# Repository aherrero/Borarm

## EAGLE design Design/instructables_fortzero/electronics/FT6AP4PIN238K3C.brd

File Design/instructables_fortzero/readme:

http://www.instructables.com/id/4-Axis-Robot-Arm-DIY/

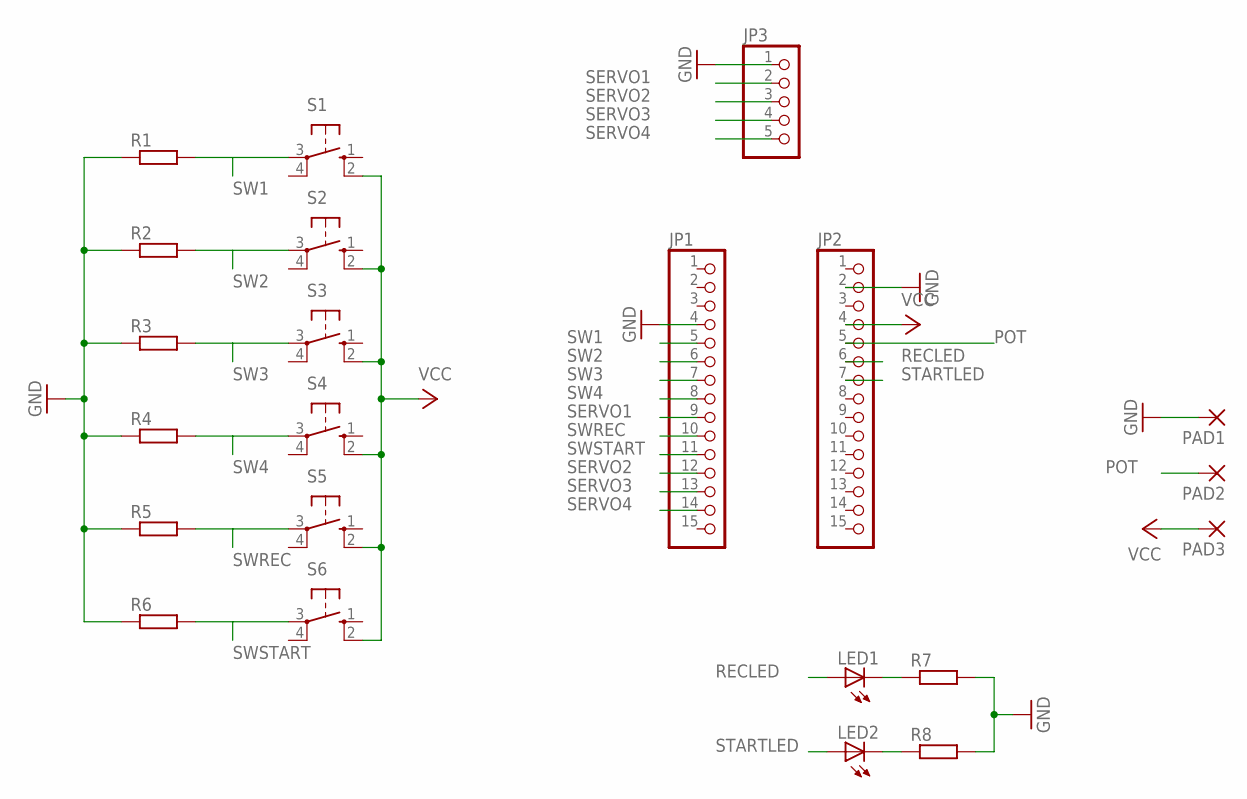
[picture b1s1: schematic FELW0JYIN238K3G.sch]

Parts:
JP1, JP2: PINHD-1X15; 1X15
JP3: PINHD-1X5; 1X05
LED1, LED2: LED5MM
PAD1, PAD2, PAD3: 2,54/1,0
R1, R2, R3, R4, R5, R6, R7, R8: R0207/10; 0207/10
S1, S2, S3, S4, S5, S6: 10-XX; B3F-10XX

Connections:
GND: JP1.4, JP2.2, JP3.1, PAD1.1, R1.1, R2.1, R3.1, R4.1, R5.1, R6.1, R7.2, R8.2
unnamed: LED1.K (C), R7.1
unnamed: LED2.K (C), R8.1
POT: JP2.5, PAD2.1
RECLED: JP2.6, LED1.A
SERVO1: JP1.9, JP3.2
SERVO2: JP1.12, JP3.3
SERVO3: JP1.13, JP3.4
SERVO4: JP1.14, JP3.5
STARTLED: JP2.7, LED2.A
SW1: JP1.5, R1.2, S1.3
SW2: JP1.6, R2.2, S2.3
SW3: JP1.7, R3.2, S3.3
SW4: JP1.8, R4.2, S4.3
SWREC: JP1.10, R5.2, S5.3
SWSTART: JP1.11, R6.2, S6.3
VCC: JP2.4, PAD3.1, S1.2 (S1), S2.2 (S1), S3.2 (S1), S4.2 (S1), S5.2 (S1), S6.2 (S1)

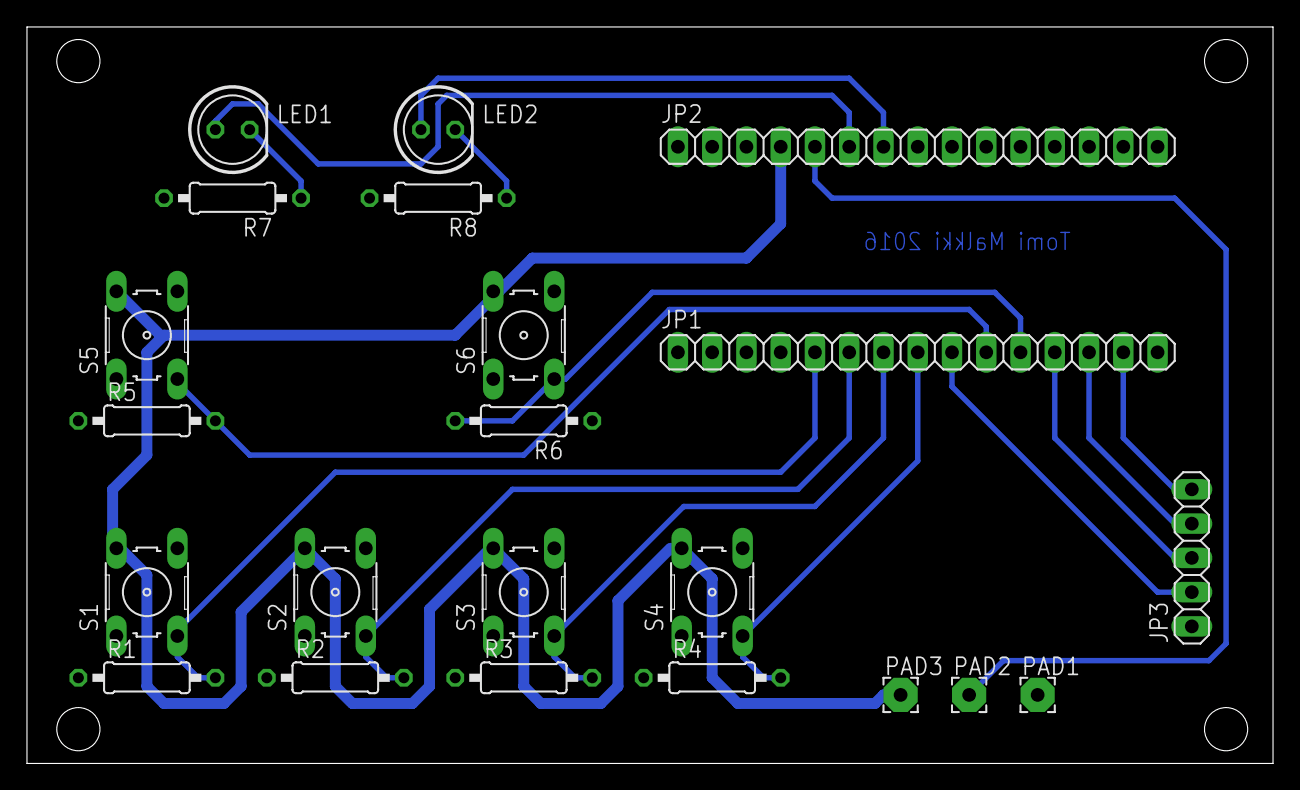
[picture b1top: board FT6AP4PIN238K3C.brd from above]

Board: 2 copper layers, 92.4 x 54.6 mm, 22 parts (0 on the bottom side), 17 nets.

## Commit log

2018-02-11 first test with servos and nunchuck
2018-02-18 only using joystick to move +5 pos each time
2018-06-01 last modifictaion..
